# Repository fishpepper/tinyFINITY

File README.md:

# tinyFINITY

This is a reference implementation for hardware for my custom OSD firmware.

See 

https://github.com/fishpepper/tinyOSD

or my blog post

https://fishpepper.de/2019/03/11/tinyosd-tinyfinity-a-tiny-opensource-video-tx-with-full-graphic-osd

for more details.

This work is published under the CERN open hardware license v1.2. 
Feel free to use the design - but make sure to give proper credit 
and release all modifications under the same license! 
See LICENSE for details!

THIS COMES WITH NO WARRANTY! BUILD, FLY, AND USE AT YOUR OWN RISK!

# Build your own

Make sure to init the git submodule for the libraries in the
kicad_misc directory by calling git submodule init && git submodule update.
You will have to use a recent kicad version, i used the commit #efdfaeb
when i designed this circuit board. Older versions will probably not work.

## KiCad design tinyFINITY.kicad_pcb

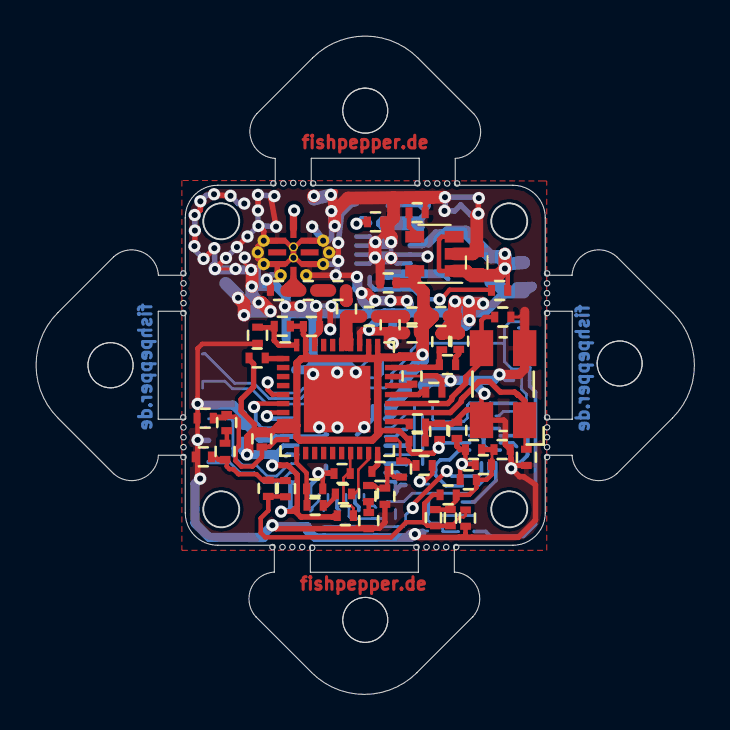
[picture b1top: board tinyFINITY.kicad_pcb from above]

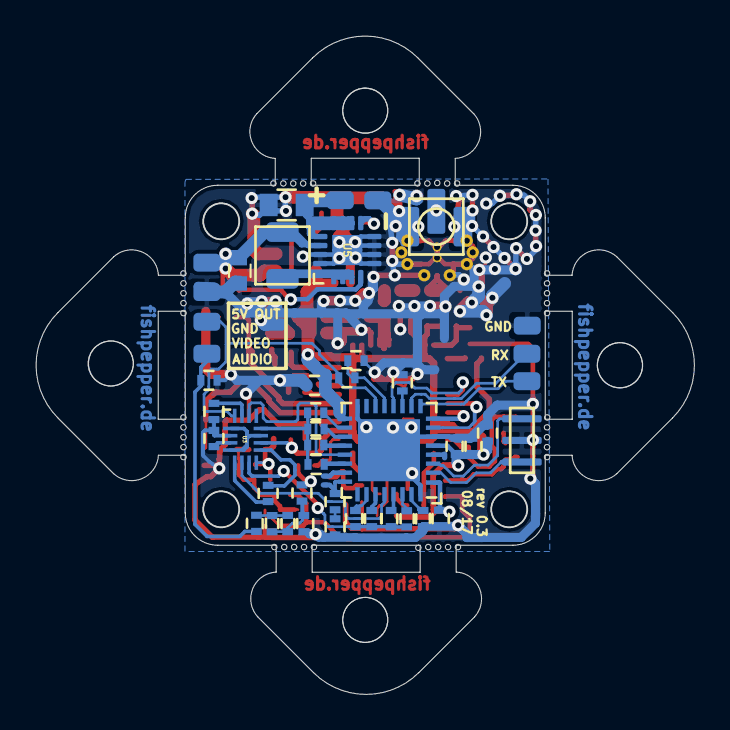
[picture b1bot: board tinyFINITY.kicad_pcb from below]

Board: 2 copper layers, 36.5 x 36.5 mm, 155 parts (48 on the bottom side), 73 nets.

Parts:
ANT1: COAX; U.FL-R-SMT-1
C1: 470pF; C_0402_CUSTOM
C2, C13, C22, C33: 4.7uF; C_0402_CUSTOM
C3, C7, C11, C23, C34, C39: 1uF; C_0402_CUSTOM
C4: 1nF; C_0402_CUSTOM
C5: 20pF; C_0402_CUSTOM
C6: 6.2pF; C_0402_CUSTOM
C8: '3.3pF; C_0402_CUSTOM
C9, C14, C15: '10pF; C_0402_CUSTOM
C10: 10uF; C_0402_CUSTOM
C12, C16, C19: 470nF; C_0402_CUSTOM
C17: 2.2uF; C_0402_CUSTOM
C18, C20: 33pF; C_0402_CUSTOM
C21: 3.3nF; C_0402_CUSTOM
C24, C25: 10pF; C_0402_CUSTOM
C26: 100pF; C_0402_CUSTOM
C27, C29: 820pF; C_0402_CUSTOM
C28: 1uF / 25V; C_0603_CUSTOM
C30: 47pF; C_0402_CUSTOM
C31: 680pF; C_0402_CUSTOM
C32: 56pF; C_0402_CUSTOM
C35, C36, C37, C41: 100nF; C_0402_CUSTOM
C38, C42: 10nF; C_0402_CUSTOM
C43: 10u 25V; C_0805_CUSTOM
C44: 680pF 50V; C_0402_CUSTOM
C45: 22uF; C_0603_CUSTOM
D1: LED; L_0402_CUSTOM
H1, H2, H3, H3#2, H3#3, H3#4, H3#5, H3#6, H3#7, H3#8, H3#9, H3#10, H3#11, H3#12, H3#13, H3#14, H3#15, H3#16, H3#17, H3#18, H3#19, H3#20, H3#21, H3#22, H3#23, H3#24, H3#25, H3#26, H3#27, H3#28, H3#29, H3#30, H3#31, H3#32, H3#33, H3#34, H3#35, H3#36, H3#37, H3#38, H3#39, H3#40, H3#41, H4, H4#2, H4#3, H4#4, H4#5: hole; mouting_hole
L1, L2: '1.2nH; L_0402_CUSTOM
L3: '1nH; L_0402_CUSTOM
L4, L5: 820nH; L_0402_CUSTOM
L8: 2.2uH; L_SPM3012T
R1: 51R; R_0402_CUSTOM
R2, R11: 15K; R_0402_CUSTOM
R3, R26: 3K3; R_0402_CUSTOM
R4, R10, R28: 100K; R_0402_CUSTOM
R5: 750R; R_0402_CUSTOM
R6: 10R; R_0402_CUSTOM
R7: 51K; R_0402_CUSTOM
R8: 20K; R_0402_CUSTOM
R9: 510R; R_0402_CUSTOM
R12: 47K; R_0402_CUSTOM
R13: 5.1K; R_0402_CUSTOM
R14: 82R; R_0402_CUSTOM
R15: 8R; R_0402_CUSTOM
R16: 4R; R_0402_CUSTOM
R17: 1.2K; R_0402_CUSTOM
R18: 200R; R_0402_CUSTOM
R19: 2R; R_0402_CUSTOM
R20: 10k; R_0402_CUSTOM
R21: R; R_0402_CUSTOM
R22: 1k37; R_0402_CUSTOM
R23: 10K; R_0402_CUSTOM
R24: 681; R_0402_CUSTOM
R25: 47R; R_0402_CUSTOM
R27: 0R; R_0402_CUSTOM
R29: 510K; R_0402_CUSTOM
R30: 560K; R_0402_CUSTOM
R32: 1K; R_0402_CUSTOM
R33: 348; R_0402_CUSTOM
R34: 169; R_0402_CUSTOM
R35, R36: 75R; R_0402_CUSTOM
TP1: UART_TX; TP_1.5x1.0
TP2: UART_RX; TP_1.5x1.0
TP3: SWRESET; TP_smd_0.5x0.3
TP4: SWDATA; TP_smd_0.5x0.3
TP5: SWCLK; TP_smd_0.5x0.3
TP6: VIDEO; TP_1.5x1.0
TP7: VCC; TP_1.5x1.0
TP8, TP10, TP13: GND; TP_1.5x1.0
TP9: AUDIO_IN; TP_1.5x1.0
TP11: 5V; TP_1.5x1.0
U1: MIC5205; SOT-23-5
U2: RTC6705; QFN40_6x6_RTC
U3: ts3a44159; UQFN16
U4: STM32F301K8Ux; UFQFPN32
U5: TPS62153A-Q1; VQFN16
X1: 8MHZ 20pF 30ppm; crystal_5032
X2: 8MHz; CSTCE_G_A
Y1: LF2012-A5R5AA; LPF20125

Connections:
3V3: C2.2, C3.2, C12.1, C13.1, C14.2, C34.2, C35.1, C36.2, C37.2, C38.2, C39.2, R1.2, R3.1, R6.2, R29.2, R32.2, U1.5, U2.8, U2.9, U2.22, U2.30, U2.31, U2.32, U2.39, U3.10, U4.1, U4.5, U4.17
5V: C28.1, C45.2, L8.2, R28.2, TP11.1, U1.1, U1.3, U5.14
AUDIO: C24.1, R13.1, TP9.1
GND: ANT1.GND, C1.1, C2.1, C3.1, C4.2, C6.1, C7.2, C9.1, C10.1, C11.2, C12.2, C13.2, C14.1, C16.1, C18.2, C19.2, C20.2, C22.2, C23.2, C24.2, C25.1, C28.2, C29.1, C34.1, C35.2, C36.1, C37.1, C38.1, C39.1, C41.2, C42.2, C43.1, C44.1, C45.1, D1.1, L3.2, R9.1, R14.1, R18.1, R20.2, R30.1, R35.2, R36.2, TP8.1, TP10.1, TP13.1, U1.2, U2.28, U2.33, U2.38, U2.41, U3.2, U4.6, U4.16, U4.32, U4.33, U5.5, U5.6, U5.7, U5.8, U5.15, U5.16, U5.17, X1.2, X1.4, X2.2, Y1.1, Y1.3, Y1.5, Y1.7
LED: R25.1, TP5.1, U4.24
unnamed: ANT1.SIG, Y1.4
unnamed: C1.2, U1.4
unnamed: C4.1, R1.1, U2.40
unnamed: C5.1, R2.2
unnamed: C5.2, U2.19
unnamed: C6.2, R2.1, U2.11
unnamed: C7.1, R3.2, U2.17
unnamed: C8.1, L2.2
unnamed: C8.2, L1.1, U2.34, U2.35
unnamed: C9.2, L1.2, R6.1
unnamed: C10.2, R5.1
unnamed: C11.1, R4.1, R5.2, R7.1
unnamed: C15.1, L3.1, Y1.8
unnamed: C15.2, L2.1
unnamed: C16.2, U2.23
unnamed: C17.1, R8.2
unnamed: C17.2, R7.2, U2.21
unnamed: C18.1, U2.24, X1.1
unnamed: C19.1, U2.26
unnamed: C20.1, U2.25, X1.3
unnamed: C21.1, R11.1, R13.2
unnamed: C21.2, R8.1, R9.2, R11.2
unnamed: C22.1, R12.1
unnamed: C23.1, R10.1, R12.2, U2.29
unnamed: C26.1, C27.1, C29.2, C30.2, C31.2, L4.1, L5.2
unnamed: C30.1, C31.1, C32.1, L5.1, R14.2, R17.2
unnamed: C32.2, C33.2, R17.1, R18.2
unnamed: C33.1, R26.2
unnamed: C41.1, U4.11
unnamed: C42.1, R23.1, U4.13
unnamed: C44.2, U5.9
unnamed: D1.2, R25.2
unnamed: L8.1, U5.1, U5.2, U5.3
unnamed: R4.2, U2.20
unnamed: R10.2, U2.27
unnamed: R20.1, U4.31
unnamed: R26.1, R29.1, R30.2, U2.10
unnamed: R27.1, U3.5
unnamed: R27.2, U3.9
unnamed: R28.1, U5.4
unnamed: R32.1, U2.1
unnamed: R35.1, U3.15
unnamed: R36.1, U3.3
unnamed: U3.1, U3.4, U3.11
unnamed: U4.2, X2.1
unnamed: U4.3, X2.3
SPI_CS: U2.6, U4.7
SPI_MOSI: U2.5, U4.12
SPI_SCK: U2.7, U4.8
SWDATA: TP4.1, U4.23
SWRESET: TP3.1, U4.4
UART_RX: TP2.1, U4.10
UART_TX: TP1.1, U4.9
VIDEO_IN: R23.2, TP6.1, U3.16, U4.14
VIDEO_OUT: C25.2, C26.2, C27.2, L4.2, U3.8
VIDEO_OVERLAY_BLACK: U3.6, U4.28
VIDEO_OVERLAY_WHITE: U3.14, U4.21
VIN: C43.2, TP7.1, U5.10, U5.11, U5.12, U5.13
V_BLACK: R22.1, R24.1, R33.1, R34.1, U3.7
V_BLACK_0: R22.2, U4.26
V_BLACK_1: R24.2, U4.27
V_BLACK_2: R33.2, U4.29
V_BLACK_3: R34.2, U4.30
V_WHITE: R15.2, R16.2, R19.2, R21.2, U3.12
V_WHITE_0: R15.1, U4.18
V_WHITE_1: R16.1, U4.19
V_WHITE_2: R19.1, U4.20
V_WHITE_3: R21.1, U4.22

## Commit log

2017-05-24 added sch
2017-05-27 added pcb
2017-05-27 board outline
2017-06-02 some routing
2017-06-03 fixed design rules
2017-06-04 some routing cleanup
2017-06-05 routing done
2017-06-05 changed parts
2017-06-06 some tweaks
2017-06-23 none
2017-06-23 cleanup
2017-06-23 footprint fix
2017-06-23 fixed L
2017-08-30 backup
2017-09-04 multitabs
2019-03-11 added lic+readme
